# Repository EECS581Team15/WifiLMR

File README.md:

# WifiLMR
A land mobile radio-like product for unlicensed campus-wide use.

Getting Started
---------------

### Python Projects

1. Be on a GNU/Linux system, preferably a Debian-derivative (such as Ubuntu or Mint).
2. Make sure Python 3.x (where x >= 6) is installed.
3. Install pip (`sudo apt install python3-pip`)
4. Install virtualenv (`pip3 install --user virtualenv`)
5. Make a virtual environment for each project:
    * **radiomanager**: $REPO/env-man (`virtualenv env-man`)
    * **radioapp**: $REPO/env-app (`virtualenv env-app`)
6. Enter the environment for the project you're working on (`source env-$PROJ/bin/activate`)
7. Install libdbus (`sudo apt install libdbus-glib-1-dev`)
8. Restore the project dependencies (`pip install -r requirements.txt` in the corresponding folder)

### Radio Firmware

1. Sync git submodules (`git submodule init && git submodule update`)
2. Enter the `boardsupport/buildroot directory`
3. Execute `make BR2_EXTERNAL=../bsp wifilmr_defconfig`
4. Execute `make`
5. Go get coffee.
6. Write `boardsupport/buildroot/output/images/sdcard.img` to a MicroSD card.

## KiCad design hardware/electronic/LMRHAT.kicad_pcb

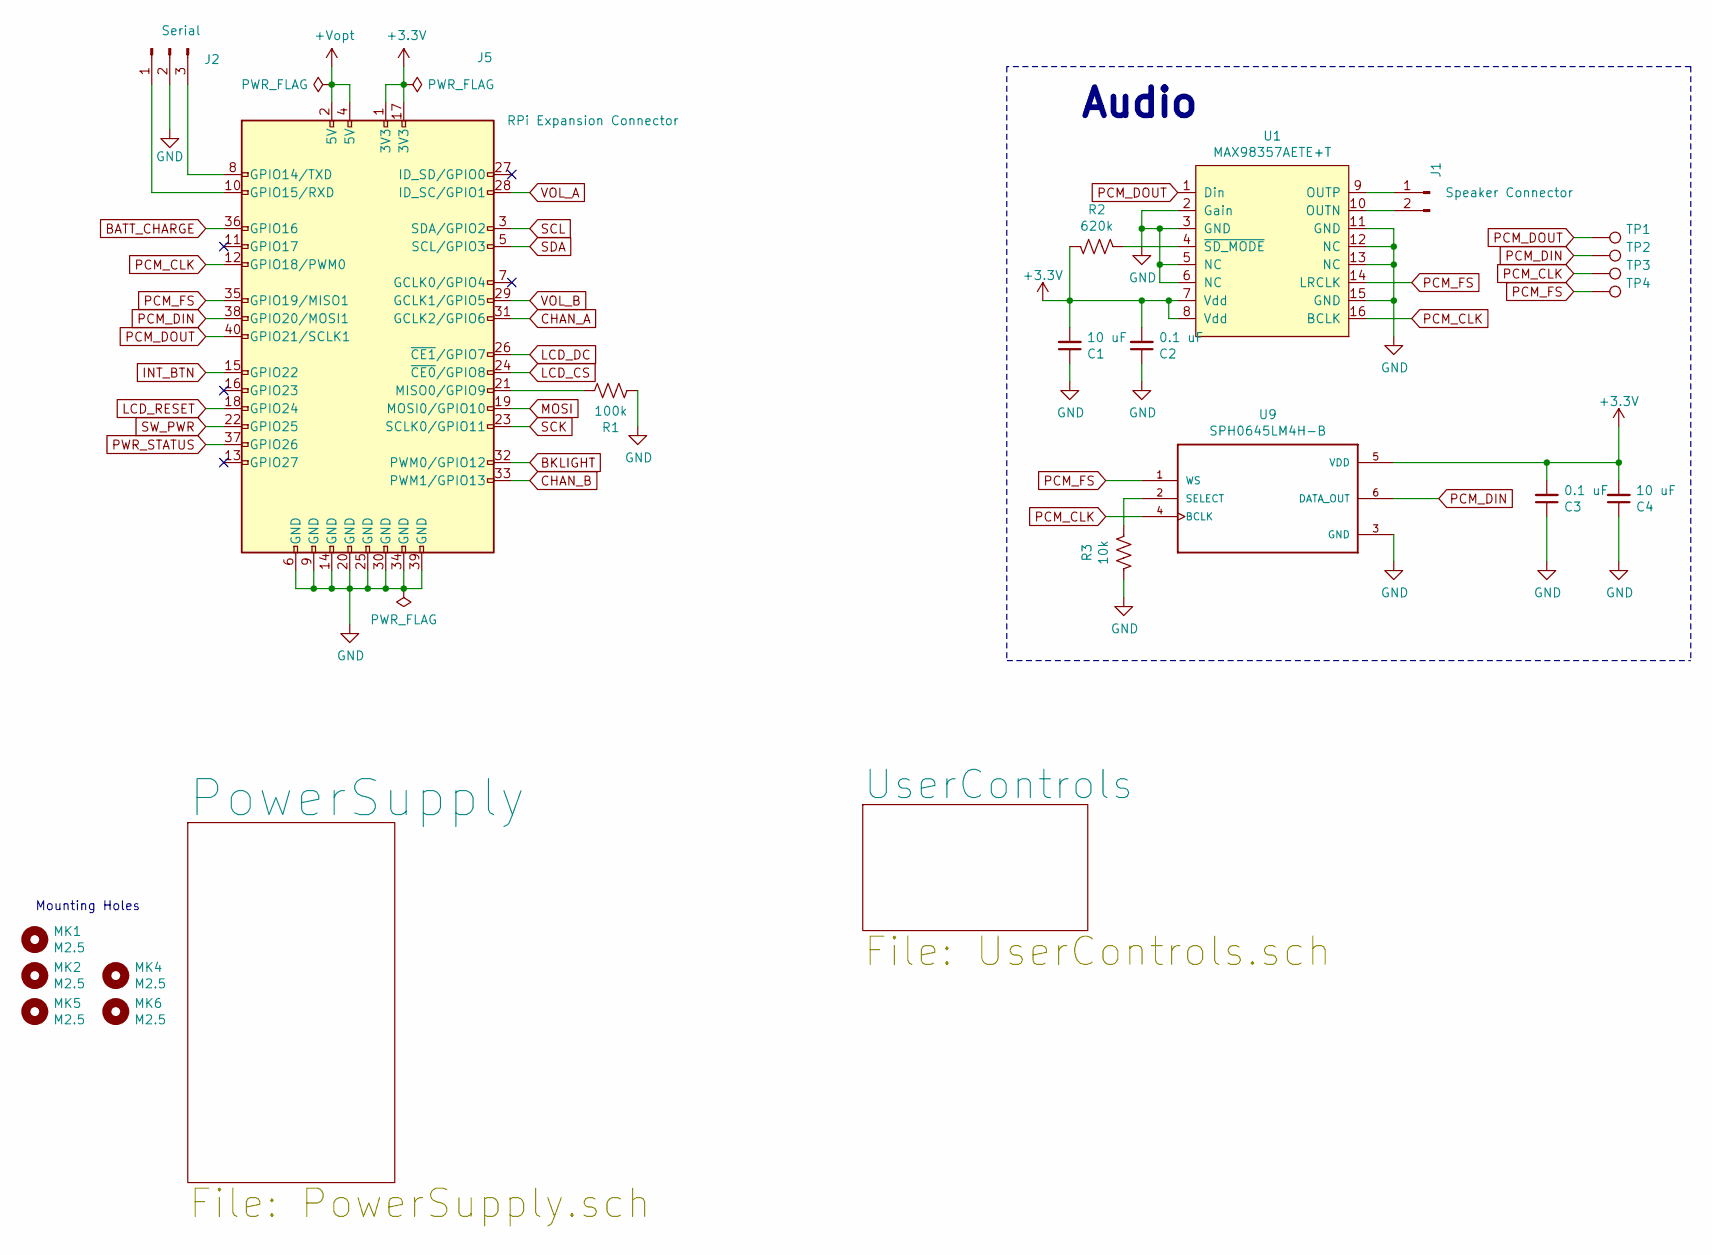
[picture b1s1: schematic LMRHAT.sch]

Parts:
C1, C4: 10 uF; C_1206_3216Metric_Pad1.42x1.75mm_HandSolder
C2, C3: 0.1 uF; C_1206_3216Metric_Pad1.42x1.75mm_HandSolder
J1: Speaker Connector; JST_EH_B02B-EH-A_1x02_P2.50mm_Vertical
J2: Serial; PinSocket_1x03_P2.54mm_Vertical
J5: RPi Expansion Connector; PinSocket_2x20_P2.54mm_Vertical_SMD
MK1, MK2, MK4, MK5, MK6: M2.5; MountingHole_2.7mm_M2.5
R1: 100k; R_1206_3216Metric_Pad1.42x1.75mm_HandSolder
R2: 620k; R_1206_3216Metric_Pad1.42x1.75mm_HandSolder
R3: 10k; R_1206_3216Metric_Pad1.42x1.75mm_HandSolder
TP1, TP2, TP3, TP4: TestPoint_Pad_D1.0mm
U1: MAX98357AETE+T; QFN-16-1EP_3x3mm_P0.5mm_EP1.8x1.8mm
U9: SPH0645LM4H-B; MIC_SPH0645LM4H-B

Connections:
+3V3: C1.2, C2.2, C3.2, C4.2, J5.1 (3V3), J5.17 (3V3), R2.1, U1.7 (Vdd), U1.8 (Vdd), U9.5 (VDD); also elsewhere on the board
+5V: J5.2 (5V), J5.4 (5V); also elsewhere on the board
BATT_CHARGE: J5.36 (GPIO16); also elsewhere on the board
BKLIGHT: J5.32 (PWM0/GPIO12); also elsewhere on the board
CHAN_A: J5.31 (GCLK2/GPIO6); also elsewhere on the board
CHAN_B: J5.33 (PWM1/GPIO13); also elsewhere on the board
INT_BTN: J5.15 (GPIO22); also elsewhere on the board
LCD_CS: J5.24 (~CE0~/GPIO8); also elsewhere on the board
LCD_DC: J5.26 (~CE1~/GPIO7); also elsewhere on the board
LCD_RESET: J5.18 (GPIO24); also elsewhere on the board
MOSI: J5.19 (MOSI0/GPIO10); also elsewhere on the board
unnamed: J1.1, U1.9 (OUTP)
unnamed: J1.2, U1.10 (OUTN)
unnamed: J2.1, J5.10 (GPIO15/RXD)
unnamed: J2.3, J5.8 (GPIO14/TXD)
unnamed: J5.21 (MISO0/GPIO9), R1.1
unnamed: R3.2, U9.2 (SELECT)
PCM_CLK: J5.12 (GPIO18/PWM0), TP3.1, U1.16 (BCLK), U9.4 (BCLK)
PCM_DIN: J5.38 (GPIO20/MOSI1), TP2.1, U9.6 (DATA_OUT)
PCM_DOUT: J5.40 (GPIO21/SCLK1), TP1.1, U1.1 (Din)
PCM_FS: J5.35 (GPIO19/MISO1), TP4.1, U1.14 (LRCLK), U9.1 (WS)
PWR_STATUS: J5.37 (GPIO26); also elsewhere on the board
SCK: J5.23 (SCLK0/GPIO11); also elsewhere on the board
SCL: J5.3 (SDA/GPIO2); also elsewhere on the board
SDA: J5.5 (SCL/GPIO3); also elsewhere on the board
SW_PWR: J5.22 (GPIO25); also elsewhere on the board
VOL_A: J5.28 (ID_SC/GPIO1); also elsewhere on the board
VOL_B: J5.29 (GCLK1/GPIO5); also elsewhere on the board

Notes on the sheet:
Mounting Holes
Audio

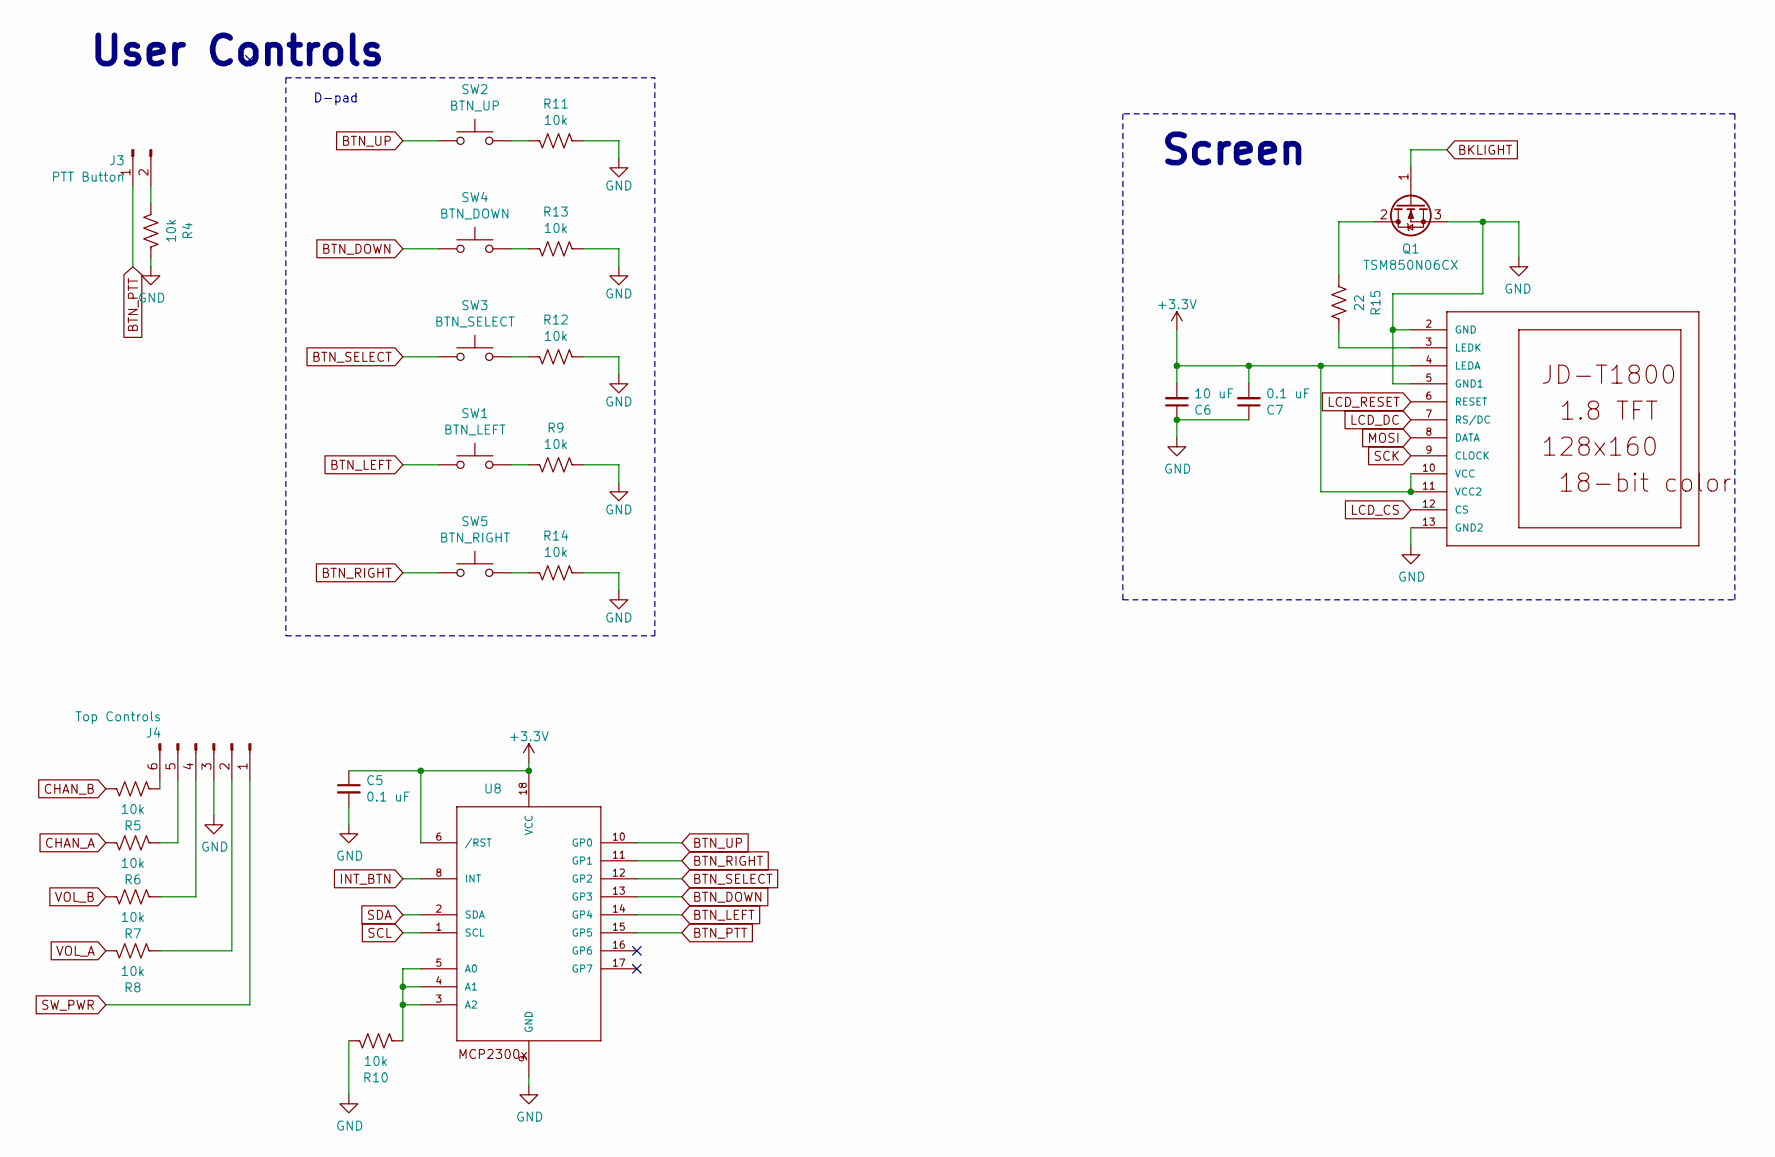
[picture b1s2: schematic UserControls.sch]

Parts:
C5, C7: 0.1 uF; C_1206_3216Metric_Pad1.42x1.75mm_HandSolder
C6: 10 uF; C_1206_3216Metric_Pad1.42x1.75mm_HandSolder
J3: PTT Button; JST_EH_B02B-EH-A_1x02_P2.50mm_Vertical
J4: Top Controls; PinHeader_2x03_P2.54mm_Vertical
LCD1: JD-T1800
Q1: TSM850N06CX; SOT-23_Handsoldering
R4, R5, R6, R7, R8, R9, R10, R11, R12, R13, R14: 10k; R_1206_3216Metric_Pad1.42x1.75mm_HandSolder
R15: 22; R_1206_3216Metric_Pad1.42x1.75mm_HandSolder
SW1: BTN_LEFT; SW_PUSH_6mm_H5mm
SW2: BTN_UP; SW_PUSH_6mm_H5mm
SW3: BTN_SELECT; SW_PUSH_6mm_H5mm
SW4: BTN_DOWN; SW_PUSH_6mm_H5mm
SW5: BTN_RIGHT; SW_PUSH_6mm_H5mm
U8: MCP23008_SO; SOIC-18W_7.5x11.6mm_P1.27mm

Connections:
+3V3: C5.1, C6.2, C7.2, LCD1.4 (LEDA), LCD1.10 (VCC), LCD1.11 (VCC2), U8.6 (/RST), U8.18 (VCC); also elsewhere on the board
BKLIGHT: Q1.1 (G); also elsewhere on the board
BTN_DOWN: SW4.1, U8.13 (GP3)
BTN_LEFT: SW1.1, U8.14 (GP4)
BTN_PTT: J3.1, U8.15 (GP5)
BTN_RIGHT: SW5.1, U8.11 (GP1)
BTN_SELECT: SW3.1, U8.12 (GP2)
BTN_UP: SW2.1, U8.10 (GP0)
CHAN_A: R6.2; also elsewhere on the board
CHAN_B: R5.2; also elsewhere on the board
INT_BTN: U8.8 (INT); also elsewhere on the board
LCD_CS: LCD1.12 (CS); also elsewhere on the board
LCD_DC: LCD1.7 (RS/DC); also elsewhere on the board
LCD_RESET: LCD1.6 (RESET); also elsewhere on the board
MOSI: LCD1.8 (DATA); also elsewhere on the board
unnamed: J3.2, R4.1
unnamed: J4.2, R8.1
unnamed: J4.4, R7.1
unnamed: J4.5, R6.1
unnamed: J4.6, R5.1
unnamed: LCD1.3 (LEDK), R15.1
unnamed: Q1.2 (D), R15.2
unnamed: R9.1, SW1.2
unnamed: R10.1, U8.3 (A2), U8.4 (A1), U8.5 (A0)
unnamed: R11.1, SW2.2
unnamed: R12.1, SW3.2
unnamed: R13.1, SW4.2
unnamed: R14.1, SW5.2
SCK: LCD1.9 (CLOCK); also elsewhere on the board
SCL: U8.1 (SCL); also elsewhere on the board
SDA: U8.2 (SDA); also elsewhere on the board
SW_PWR: J4.1; also elsewhere on the board
VOL_A: R8.2; also elsewhere on the board
VOL_B: R7.2; also elsewhere on the board

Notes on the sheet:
D-pad
User Controls
Screen

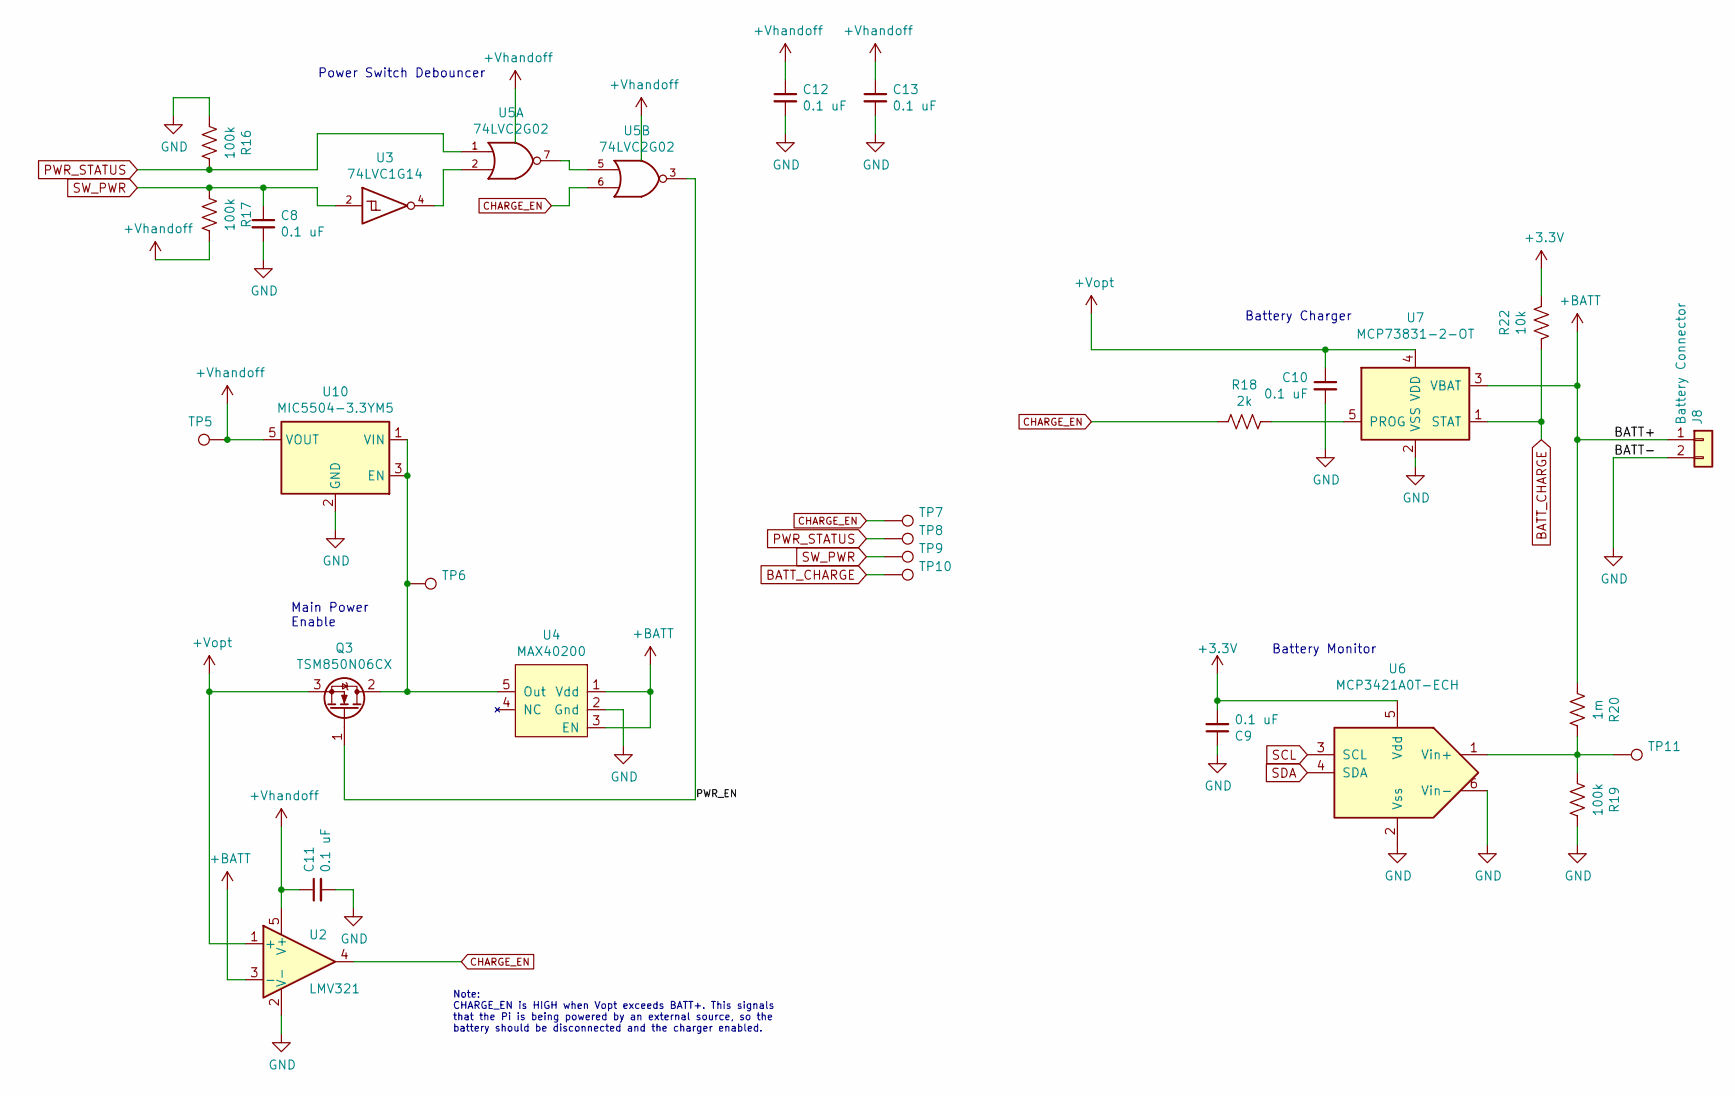
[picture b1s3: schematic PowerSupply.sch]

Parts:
C8, C9, C10, C11, C12, C13: 0.1 uF; C_1206_3216Metric_Pad1.42x1.75mm_HandSolder
J8: Battery Connector; JST_EH_B02B-EH-A_1x02_P2.50mm_Vertical
Q3: TSM850N06CX; SOT-23_Handsoldering
R16, R17, R19: 100k; R_1206_3216Metric_Pad1.42x1.75mm_HandSolder
R18: 2k; R_1206_3216Metric_Pad1.42x1.75mm_HandSolder
R20: 1m; R_1206_3216Metric_Pad1.42x1.75mm_HandSolder
R22: 10k; R_1206_3216Metric_Pad1.42x1.75mm_HandSolder
TP5, TP6, TP7, TP8, TP9, TP10, TP11: TestPoint_Pad_D1.0mm
U2: LMV321; SOT-23-5_HandSoldering; Digikey 497-13051-1-ND
U3: 74LVC1G14; SOT-353_SC-70-5_Handsoldering; Digikey 74LVC1G14SE-7CT-ND
U4: MAX40200; SOT-23-5_HandSoldering
U5: 74LVC2G02; TSSOP-8_3x3mm_P0.65mm
U6: MCP3421A0T-ECH; SOT-23-6_Handsoldering
U7: MCP73831-2-OT; SOT-23-5_HandSoldering
U10: MIC5504-3.3YM5; SOT-23-5_HandSoldering

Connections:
+3V3: C9.2, R22.2, U6.5 (Vdd); also elsewhere on the board
+5V: C10.1, Q3.3 (S), U2.1 (+), U7.4 (VDD); also elsewhere on the board
+BATT: J8.1, R20.2, U2.3 (-), U4.1 (Vdd), U4.3 (EN), U7.3 (VBAT)
+handoff: C11.1, C12.1, C13.1, R17.1, TP5.1, U2.5 (V+), U3.5 (VCC), U5.8 (VCC), U10.5 (VOUT)
/PowerSupply/PWR_EN: Q3.1 (G), U5.3
BATT_CHARGE: R22.1, TP10.1, U7.1 (STAT); also elsewhere on the board
CHARGE_EN: R18.2, TP7.1, U2.4, U5.6
unnamed: Q3.2 (D), TP6.1, U4.5 (Out), U10.1 (VIN), U10.3 (EN)
unnamed: R18.1, U7.5 (PROG)
unnamed: R19.2, R20.1, TP11.1, U6.1 (Vin+)
unnamed: U3.4, U5.2
unnamed: U5.5, U5.7
PWR_STATUS: R16.1, TP8.1, U5.1; also elsewhere on the board
SCL: U6.3 (SCL); also elsewhere on the board
SDA: U6.4 (SDA); also elsewhere on the board
SW_PWR: C8.1, R17.2, TP9.1, U3.2; also elsewhere on the board

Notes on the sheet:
Battery Charger
Battery Monitor
Main Power Enable
Power Switch Debouncer
Note: CHARGE_EN is HIGH when Vopt exceeds BATT+. This signals that the Pi is being powered by an external source, so the battery should be disconnected and the charger enabled.

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
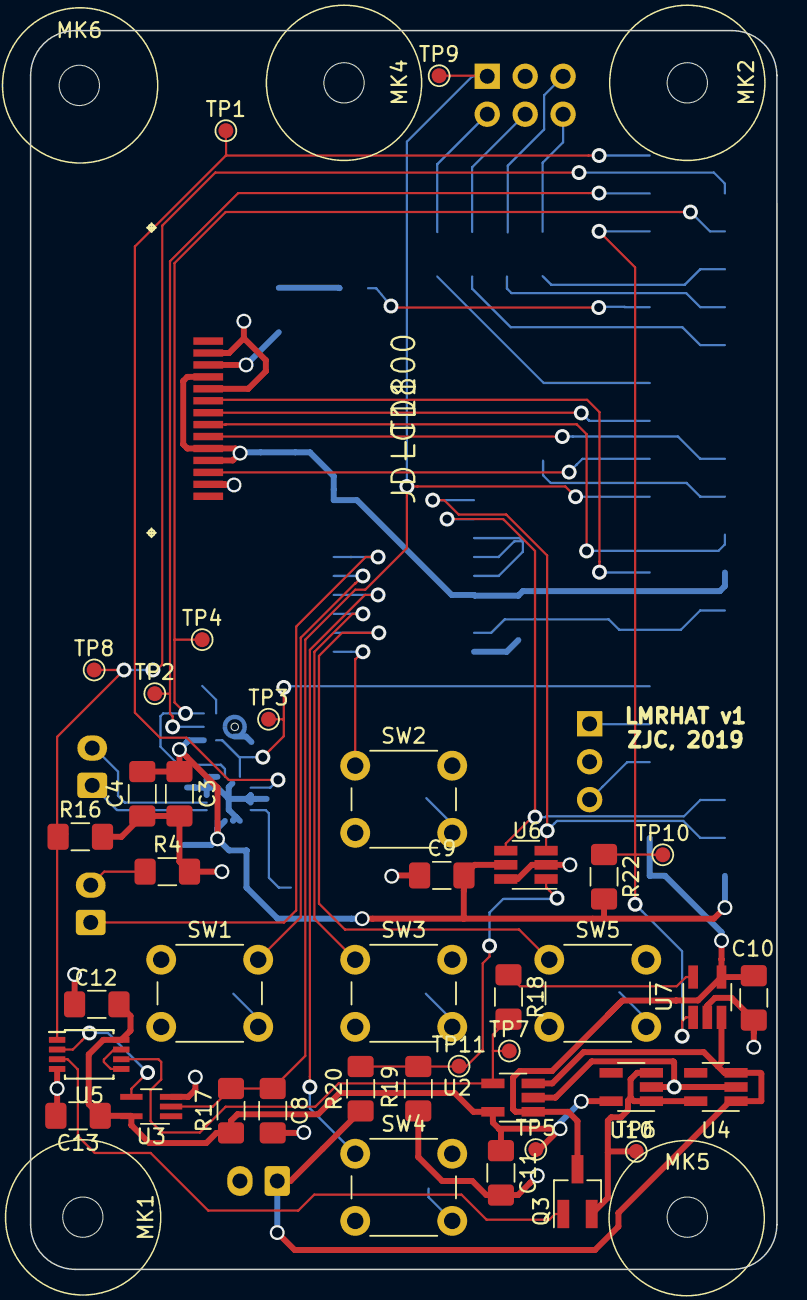
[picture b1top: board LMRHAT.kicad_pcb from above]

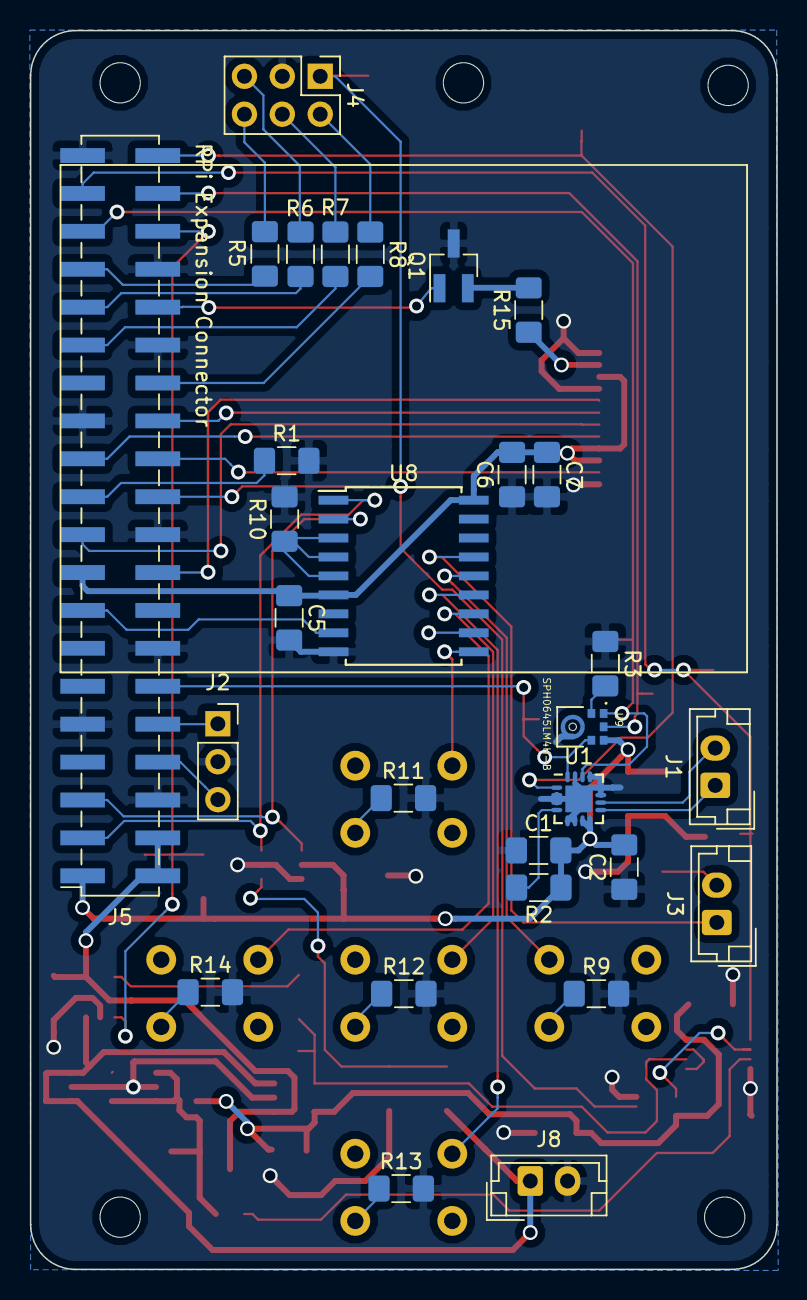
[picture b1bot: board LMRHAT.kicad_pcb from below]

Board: 2 copper layers, 50.0 x 83.0 mm, 74 parts (29 on the bottom side), 58 nets.

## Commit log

2018-10-11 #1: Initial project files
2018-10-11 #1: Added launch and debug configuration
2018-10-11 #1: Fixed a build error caused by shadowing
2018-10-11 #1: Initial commit of glossary and ui paradigm docs
2018-10-11 #1: Added note about status led
2018-10-12 #1: Added more terms to the glossary
2018-10-12 #1: Added initial software architecture document (client side only)
2018-10-14 #1: Added provisioning mode document
2018-10-14 #1: Added initial feature listing
2018-10-14 #1: Added vscode extension recommendations
2018-10-14 #1: Added short notes about environment setup and building
2018-10-19 #1: Added basic pull request template
2018-10-19 #1: Fixed markdown formatting
2018-10-25 #20: Removed .NET projects and related files
2018-10-25 #20: Changed recommended vscode extensions to python
2018-10-25 #20: Changed top-level gitignore to python
2018-10-25 #20: Removed .NET configurations from launch.json
2018-10-25 #20: Added Python project skeleton
2018-10-29 unstyled homescrean
2018-10-31 Empty Settings Page
2018-11-02 Initial Flask setup
2018-11-03 renaming & reference holding
2018-11-10 #27: Moved radiomanager down one folder level to ease development
2018-11-10 #27: Added initial flask-restful API endpoint
2018-11-10 #27: Added SQLAlchemy and re-arranged app initialization
2018-11-12 #27: Added Flask-Testing and cryptography dependencies
2018-11-12 #27: Added Device DB model
2018-11-12 #27: Added initial provisioning endpoint and tests
2018-11-12 #27: Reworked backend startup to facilitate testing
2018-11-16 Update ui_manager.py
    Docstring
2018-11-16 Docstring
2018-11-16 #27: Added notes on backend software architecture
2018-11-23 #27: Added a UUID type adapter for sqlalchemy
2018-11-23 #27: Added a unique uuid field to provision endpoint and db model
2018-11-23 #31: Added mDNS service registration via avahi
2018-11-23 Updated README for getting started with Python development
2018-11-23 #18: Added buildroot 2018.02.2 as a git submodule
2018-11-28 #18: Added a BR2_EXTERNAL directory for our board
2018-11-29 Added requirements for pymumble
2018-11-29 mumble adapter
2018-11-29 pymumble added
2018-11-29 python stuff
2018-11-29 callbacks
2018-11-29 #39: Added a document about adding project dependencies
2018-11-29 #39: Moved all radioapp files down one directory for easier packaging
2018-11-29 #39: Added a buildroot package for radioapp
2018-11-29 #39: Added an init script for radioapp
2018-11-29 #39: Added a setup.py for radioapp
2018-11-29 #39: Formatted radioapp.ui and corrected identation errors
2018-11-30 #39: Switched to our own copy of buildroot
2018-11-30 #39: Corrected radioapp buildroot package file
2018-11-30 #39: Selected radioapp and dependencies in buildroot
2018-12-02 UI Backlight
2018-12-03 Added Kicad gitignore from Github
2018-12-03 Added adafruit and snapeda library files
2018-12-03 Added library of modified footprints
2018-12-03 Added initial schematic and PCB designs
2018-12-03 Connected power switch to a GPIO and moved the layout for readability
2018-12-05 added service discovery foundation
2018-12-05 removed uncessary ip variable
2018-12-05 removed ip variable in listener initialization
2018-12-05 pull request suggestions but unclear of information use
2018-12-05 installed pymumble_py3 locally
2018-12-05 Added source for pymumble in doc
2018-12-05 Management Console Template Uploaded
2018-12-07 Main
2018-12-07 UI Manager and Home files
2018-12-14 Update ui_manager.py
    Documented Action Number.
2019-01-27 Rescued schematic symbols since LMRHAT.lib didn't get saved
2019-01-28 Minor spelling change
2019-01-29 Minimal wrapper for starting mumble
2019-01-30 Updates for logger, callbacks, encapsulation, and debugger
2019-02-05 Updated layout and schematic to match board dimensions of 50x80mm
2019-02-05 #33: Added initial OpenSCAD casing design.
2019-02-06 Updated Button Size
2019-02-06 Updated UI Manager
2019-02-06 Fixed syntax error.
2019-02-09 driver and new calback
2019-02-13 #39: Added a post install step to radioapp to make init script executable
2019-02-13 #39: Cleaned up linux_defconfig by saving properly
2019-02-13 #39: Added a boot splash screen and init script for loading the display
2019-02-13 #39: Converted boot splash to BMP3 and added note about BMP formats
2019-02-13 #39: Converted SPI master from module to builtin
2019-02-13 #39: Updated buildroot tree to enable SPI in device tree
2019-02-13 #39: Fixed splash screen init script to use correct FB
2019-02-13 changing the settings.json code back to original
2019-02-13 added new requested changes and autopep8 checks
2019-02-14 #39: Various fixes to radioapp init script
2019-02-14 #39: Enabled rootfs_overlay in buildroot
2019-02-14 #39: Overrode xorg.conf to use the SPI display FB
2019-02-14 #39: Modified the radioapp package file to be a "local" package
2019-02-14 #39: Updated buildroot submodule to latest
2019-02-14 #15: Moved LmrListener class up so that it is available for use
2019-02-14 #15: Changed service name to match backend
2019-02-14 #15: Changed backend service registration to advertise on all interfaces correctly
2019-02-14 #15: Corrected a misspelling
2019-02-18 Testing
2019-02-18 more testing
2019-02-18 Added files for Backlight.
2019-02-20 Moved Manamgent Console to Radio Manager
2019-02-20 Added requirements
2019-02-20 Abstraction for pymumble
2019-02-20 Added SoundManager
2019-02-21 #59: Added custom RPi firmware config.txt with PWM enabled
2019-02-21 #59: Updated buildroot submodule to latest
2019-02-21 #59: Added initial backlight HAL implementation
2019-02-21 Added connect
2019-02-21 Added example for how to start sound_in
2019-02-25 UI Backlight modification
2019-02-27 #59: Reduced rootfs size for faster flashing
2019-02-27 #59: Disabled buildroot's python pre-compilation support
2019-02-27 #59: Added pwm driver load to radioapp init script
2019-02-27 #59: Fixed various issues in radioapp backlight driver
2019-02-27 #59: Added hack to main.py to set backlight to 100%
2019-02-27 Added templating
2019-02-27 Moved FlaskExtensions out
2019-03-06 #19: Added initial wpa_supplicant support to radioapp
2019-03-06 #19: Added icons for the wifi icon
2019-03-06 #19: Added a HAL instance holder class
2019-03-06 #19: Implemented the wifi status icon
2019-03-07 #19: Added dbus, wpa_supplicant, and other dependencies to buildroot config
2019-03-07 Rescued ui_backlight.py from a failed merge
2019-03-07 #19: Fixed merge of main.py
2019-03-07 #29: Moved backlight HAL instance in HAL holder
2019-03-07 #29: Integrated backlight menu with HAL
2019-03-07 #32: Bound keyboard controls for the home screen
2019-03-07 #32: Bound a key for exiting the backlight screen
2019-03-07 #19: Overrode DBus service file and configuration for wpa_supplicant
2019-03-07 Icons Images
2019-03-07 Added Button Icons
2019-03-09 Added Icons
2019-03-09 Base64 Icons
2019-03-11 #19: Fixed a goofed up merge. Oops
2019-03-13 Nomenclature changes
2019-03-13 added input routine
2019-03-14 Added tcl to the dependencies of python3-tkinter
2019-03-14 #19: Disabled the bluetooth to renable serial console
2019-03-14 #19: Load the wifi driver before radioapp
2019-03-14 #71: Remapped screen gpios to match design and removed splash screen
2019-03-15 #19: Added a check on the interface state to prevent the console from being flooded with errors
2019-03-15 #19: Changed "avg-rssi" to "rssi" in the UI
2019-03-15 #19: Modified wpa_supplicant.conf to connect to WifiLMRDemo as an open network
2019-03-15 #19: Added init script for dhcp client
2019-03-15 #19: Moved wifi module loading earlier to avoid race with udhcpc
2019-03-15 #19: Added the ability to signal udhcpc to release/renew when needed
2019-03-15 #19: Added some wifi debugging tools to the buildroot config
2019-03-16 #77: Initial device tree overlay with playback support
2019-03-17 Thread that gets input sound
2019-03-18 #77: Attempted to force sample rate to 48000
2019-03-18 #77 Added alsa configuration to rootfs
2019-03-18 more changes
2019-03-18 sound working!
2019-03-18 #77: Added automatic sound module loading
2019-03-20 base class and object call for html display through djang/flask
2019-03-20 dbus implementation: has some runtime errors I think related to murmur
2019-03-27 prevents soundplay from sleeping.
2019-03-27 Comments
2019-03-27 File move
2019-03-29 Battery Icon Added
2019-03-31 Ability to play wav file.
2019-03-31 Moved pyaudio instance into class
2019-04-02 Reconfigured DBUS
2019-04-03 DBus now works correctly. Connected devices listed
2019-04-04 #77: Converted all device tree overlays to patches
2019-04-10 made some of the pull request changes
2019-04-10 Need to check with connection
2019-04-17 #77: Hacked the spdif Linux drivers to only support the rate and format we want
2019-04-17 #77: Modified the ALSA config to boost mic volume
2019-04-20 Added dummy battery HAL
2019-04-20 Made battery icon update automatically
2019-04-20 Merged requirement.txt with requirements.txt
2019-04-21 Disabled X11 key rollover while running
2019-04-21 Reworked mumble support for better performance and multiple speakers
2019-04-21 Wired up mumble to UI
2019-04-21 Converted sound fx to use alsaaudio
2019-04-21 Implemented UI beeps and boops
2019-04-21 Made backlight setting stateful
2019-04-22 Updated setup.py to pick up wav files for sound fx
2019-04-22 Updated bootloader config for new overlays
2019-04-22 Added buildroot packages for opuslib and pymumble
2019-04-22 Added a patch for opuslib to make up for ctypes being silly
2019-04-22 Added additional dependencies to radioapp buildroot package
2019-04-22 Added device tree overlay for the MCP3421 ADC that monitors battery voltage
2019-04-22 Implemented battery adc reading in radioapp
2019-04-23 Updated buildroot configuration file
2019-04-23 Added a patch for pymumble to not stop on errors
2019-04-23 Forced /dev/urandom to think it has enough entropy to start
2019-04-23 Caught and ignored exceptions during audio recording (need better fix)
